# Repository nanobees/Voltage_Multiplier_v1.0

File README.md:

# Voltage_Multiplier_v1.0
Voltage Multiplier for AC 220V to DC 1200V

This circuit is done for converting 220V to 1200V.
For further information please contact with me: haltugyildirim_at_protonmail.com

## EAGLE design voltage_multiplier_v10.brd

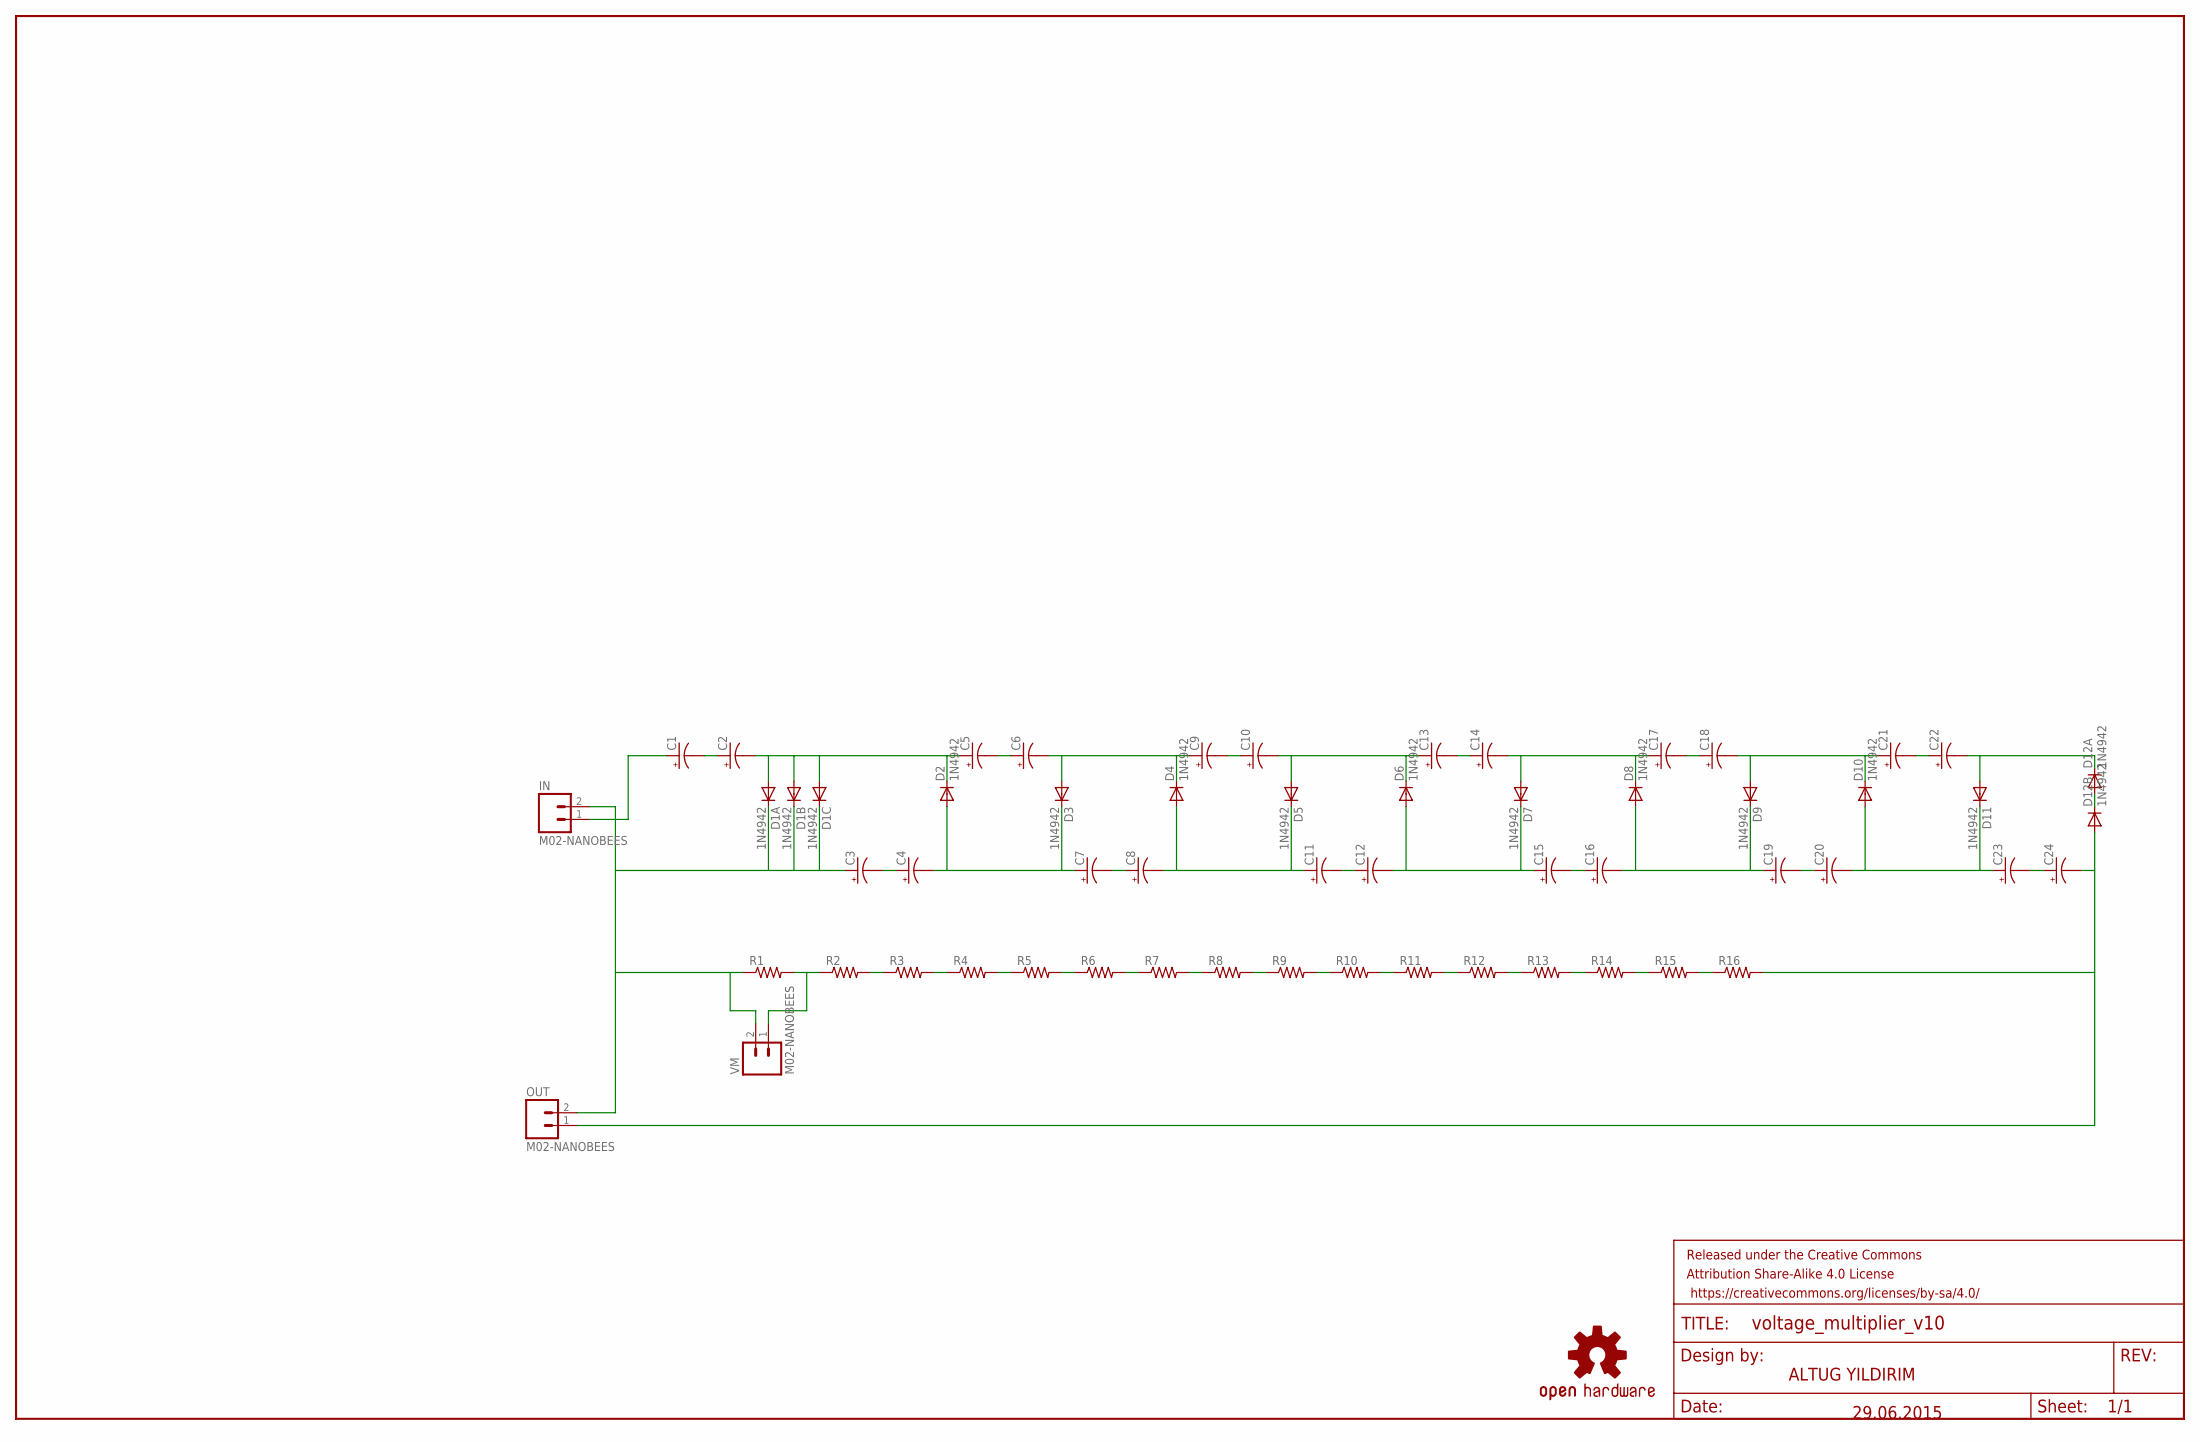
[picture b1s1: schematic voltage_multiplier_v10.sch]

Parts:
C1, C2, C3, C4, C5, C6, C7, C8, C9, C10, C11, C12, C13, C14, C15, C16, C17, C18, C19, C20, C21, C22, C23, C24: CAP_POLPTH3; CPOL-RADIAL-1000UF-63V
D1A, D1B, D1C, D2, D3, D4, D5, D6, D7, D8, D9, D10, D11, D12A, D12B: 1N4942; DO41-10
FRAME1: FRAME-LEDGER; CREATIVE_COMMONS
IN: M02-NANOBEES
LOGO1: OSHW-LOGOM; OSHW-LOGO-M
OUT: M02-NANOBEES
R1, R2, R3, R4, R5, R6, R7, R8, R9, R10, R11, R12, R13, R14, R15, R16: RESISTORPTH-1/4W; AXIAL-0.4
VM: M02-NANOBEES

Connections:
unnamed: C5.2 (-), C6.1 (+)
unnamed: C2.2 (-), C5.1 (+), D1A.A, D1B.A, D1C.A, D2.C
unnamed: C1.2 (-), C2.1 (+)
unnamed: C3.1 (+), D1A.C, D1B.C, D1C.C, IN.2, OUT.2, R1.P$1 (1), VM.2
unnamed: C3.2 (-), C4.1 (+)
unnamed: C4.2 (-), C7.1 (+), D2.A, D3.C
unnamed: C1.1 (+), IN.1
unnamed: C6.2 (-), C9.1 (+), D3.A, D4.C
unnamed: C7.2 (-), C8.1 (+)
unnamed: C9.2 (-), C10.1 (+)
unnamed: C13.2 (-), C14.1 (+)
unnamed: C8.2 (-), C11.1 (+), D4.A, D5.C
unnamed: C10.2 (-), C13.1 (+), D5.A, D6.C
unnamed: D12A.A, D12B.C
unnamed: C18.2 (-), C21.1 (+), D9.A, D10.C
unnamed: C11.2 (-), C12.1 (+)
unnamed: C12.2 (-), C15.1 (+), D6.A, D7.C
unnamed: C14.2 (-), C17.1 (+), D7.A, D8.C
unnamed: C15.2 (-), C16.1 (+)
unnamed: C17.2 (-), C18.1 (+)
unnamed: C16.2 (-), C19.1 (+), D8.A, D9.C
unnamed: C24.2 (-), D12B.A, OUT.1, R16.P$2 (2)
unnamed: C21.2 (-), C22.1 (+)
unnamed: C19.2 (-), C20.1 (+)
unnamed: C20.2 (-), C23.1 (+), D10.A, D11.C
unnamed: C22.2 (-), D11.A, D12A.C
unnamed: C23.2 (-), C24.1 (+)
unnamed: R1.P$2 (2), R2.P$1 (1), VM.1
unnamed: R2.P$2 (2), R3.P$1 (1)
unnamed: R3.P$2 (2), R4.P$1 (1)
unnamed: R4.P$2 (2), R5.P$1 (1)
unnamed: R5.P$2 (2), R6.P$1 (1)
unnamed: R6.P$2 (2), R7.P$1 (1)
unnamed: R7.P$2 (2), R8.P$1 (1)
unnamed: R8.P$2 (2), R9.P$1 (1)
unnamed: R9.P$2 (2), R10.P$1 (1)
unnamed: R10.P$2 (2), R11.P$1 (1)
unnamed: R11.P$2 (2), R12.P$1 (1)
unnamed: R12.P$2 (2), R13.P$1 (1)
unnamed: R13.P$2 (2), R14.P$1 (1)
unnamed: R14.P$2 (2), R15.P$1 (1)
unnamed: R15.P$2 (2), R16.P$1 (1)

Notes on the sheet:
ALTUG YILDIRIM
29.06.2015

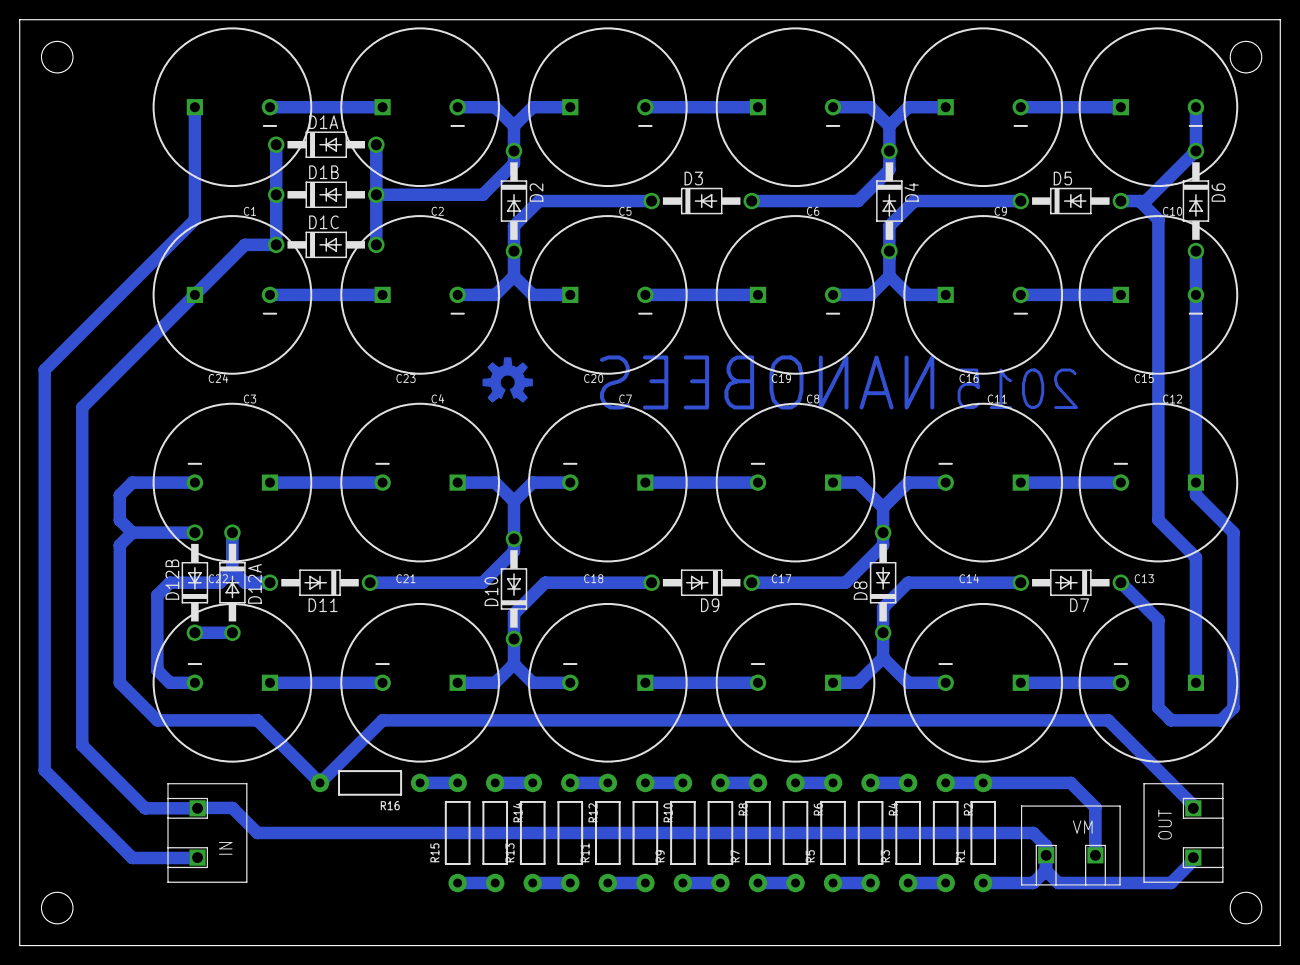
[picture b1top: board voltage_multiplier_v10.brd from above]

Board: 2 copper layers, 127.9 x 94.0 mm, 60 parts (0 on the bottom side), 42 nets.

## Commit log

2016-08-26 add initial design files
    add initial files

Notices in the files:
parts and their libraries:
SparkFun-Capacitors: Licensing: Creative Commons ShareAlike 4.0 International - https://creativecommons.org/licenses/by-sa/4.0
SparkFun-Aesthetics: Released under the Creative Commons Attribution Share-Alike 4.0 License
SparkFun-Aesthetics: https://creativecommons.org/licenses/by-sa/4.0
